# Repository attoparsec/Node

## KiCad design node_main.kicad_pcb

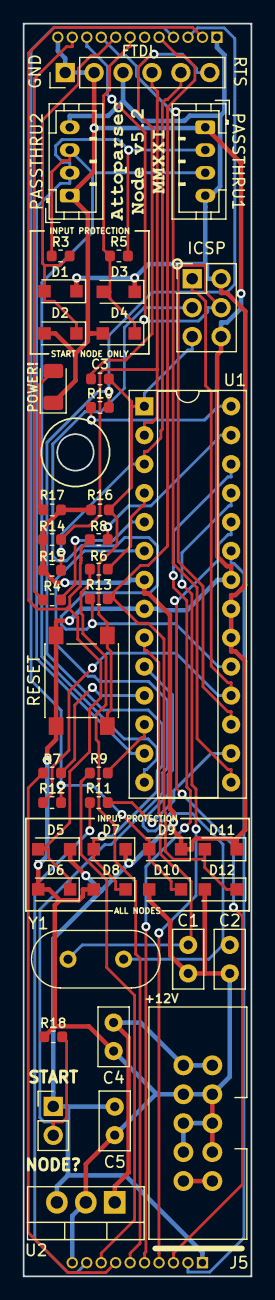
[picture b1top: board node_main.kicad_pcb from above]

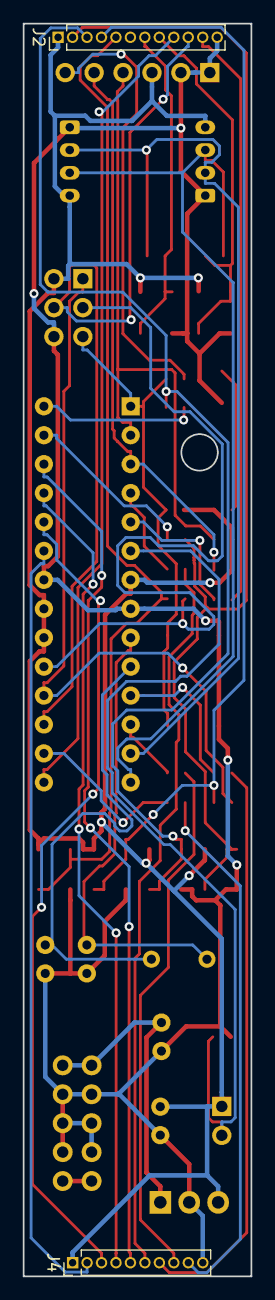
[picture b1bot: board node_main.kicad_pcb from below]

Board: 2 copper layers, 20.0 x 110.0 mm, 46 parts (2 on the bottom side), 40 nets.

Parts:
C1, C2: 22p; C_Disc_D5.0mm_W2.5mm_P2.50mm
C3: 100nF; C_0603_1608Metric
C4: 0.33U; C_Disc_D5.0mm_W2.5mm_P2.50mm
C5: 0.01U; C_Disc_D5.0mm_W2.5mm_P2.50mm
D1, D2, D3, D4, D5, D6, D7, D8, D9, D10, D11, D12: Bat85; D_SOD-123F
FTDI: FTDI; PinHeader_1x06_P2.54mm_Vertical
ICSP: Conn_02x03_Male; PinHeader_2x03_P2.54mm_Vertical
J2: Conn_01x12_Male; PinHeader_1x12_P1.27mm_Vertical
J4: Conn_01x10_Male; PinHeader_1x10_P1.27mm_Vertical
J5: Conn_02x05_Odd_Even; Shrouded_power_header
PASSTHRU1, PASSTHRU2: Conn_01x04_Male; JST_PH_B4B-PH-K_1x04_P2.00mm_Vertical
POWER!: LED; LED_1206_3216Metric
R3, R4, R5, R6, R7, R8, R9, R10, R11, R12, R13, R14, R15, R16, R17, R18: 1K; R_0603_1608Metric
RESET: SW_SPST; SW_SPST_PTS645
START1: Conn_01x02_Male; PinHeader_1x02_P2.54mm_Vertical
U1: ATmega328P-PU; DIP-28_W7.62mm_Socket
U2: L7805; TO-220-3_Vertical
Y1: Crystal; Crystal_HC49-U_Vertical

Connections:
+5V: C5.1, D1.1, D3.1, D5.1, D7.1, D9.1, D11.1, FTDI.3, ICSP.2, J2.1, J4.1, PASSTHRU1.4, PASSTHRU2.4, R14.1, R15.1, R16.1, R17.2, START1.1, U1.7, U1.20, U1.21, U2.3
+12V: C4.1, J5.1, J5.2, U2.1
-12V: J5.9, J5.10
APIN_0: J4.2, U1.23
APIN_1: J4.3, U1.24
APIN_2: J4.4, U1.25
APIN_3: J4.5, U1.26
APIN_4: R8.1, U1.27
APIN_5: R10.1, U1.28
CLOCK_MAIN: PASSTHRU1.3, PASSTHRU2.3, R3.1, U1.14
CRYSTAL1: C1.2, U1.9, Y1.1
CRYSTAL2: C2.2, U1.10, Y1.2
DPIN_2: R6.2, U1.4
DPIN_4: R18.2, START1.2, U1.6
DPIN_7: PASSTHRU1.2, PASSTHRU2.2, R5.1, U1.13
GND: C1.1, C2.1, C4.2, C5.2, D2.2, D4.2, D6.2, D8.2, D10.2, D12.2, FTDI.1, FTDI.2, ICSP.6, J2.12, J4.10, J5.3, J5.4, J5.5, J5.6, J5.7, J5.8, PASSTHRU1.1, PASSTHRU2.1, POWER!.1, R18.1, RESET.2, U1.8, U1.22, U2.2
INPUT_1_MAIN_RAW: D5.2, D6.1, J2.2, R8.2
INPUT_2_MAIN_RAW: D7.2, D8.1, J2.3, R10.2
INPUT_3_MAIN: ICSP.1, R12.1, U1.18
INPUT_3_MAIN_RAW: D9.2, D10.1, J2.4, R12.2
INPUT_4_MAIN: ICSP.3, R13.1, U1.19
INPUT_4_MAIN_RAW: D11.2, D12.1, J2.5, R13.2
INPUT_CLOCK_MAIN_RAW: D1.2, D2.1, J2.8, R3.2
INPUT_RESET_MAIN_RAW: D3.2, D4.1, J2.7, R5.2
LED_MAIN: J2.9, U1.15
MOSI_PWM_DPIN_11: ICSP.4, J2.10, U1.17
unnamed: C3.2, FTDI.6
unnamed: POWER!.2, R17.1
OUTPUT_1_MAIN_RAW: J4.6, R6.1
OUTPUT_2_MAIN: R7.2, U1.11
OUTPUT_2_MAIN_RAW: J4.7, R7.1
OUTPUT_3_MAIN: R9.2, U1.12
OUTPUT_3_MAIN_RAW: J4.8, R9.1
OUTPUT_4_MAIN: R11.2, U1.16
OUTPUT_4_MAIN_RAW: J4.9, R11.1
OUTPUT_IDENT_MAIN: R4.2, U1.5
OUTPUT_IDENT_MAIN_RAW: J2.11, R4.1
RESET: C3.1, ICSP.5, R16.2, RESET.1, U1.1
RX_DPIN_0: FTDI.4, R14.2, U1.2
TX_DPIN_1: FTDI.5, R15.2, U1.3

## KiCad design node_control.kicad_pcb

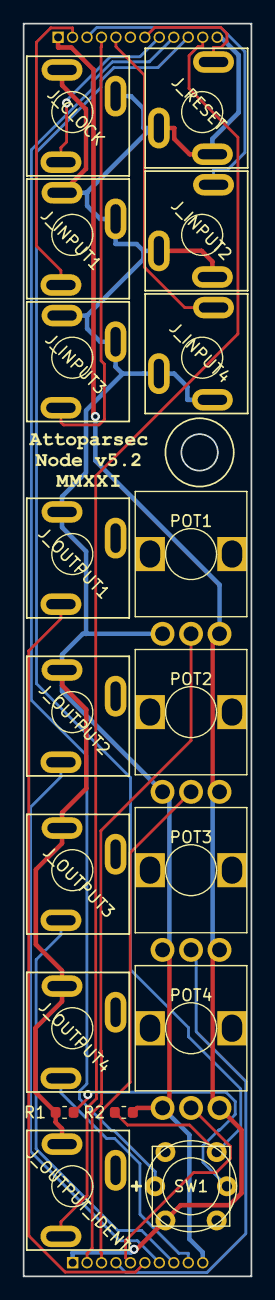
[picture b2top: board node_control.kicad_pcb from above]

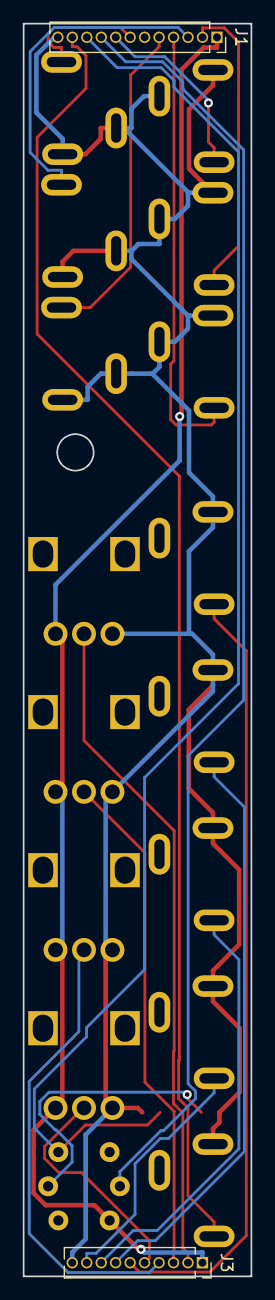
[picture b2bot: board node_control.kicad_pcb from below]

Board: 2 copper layers, 20.0 x 110.0 mm, 20 parts (2 on the bottom side), 20 nets.

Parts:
J1: Conn_01x12_Female; PinSocket_1x12_P1.27mm_Vertical
J3: Conn_01x10_Female; PinSocket_1x10_P1.27mm_Vertical
J_CLOCK: PJ301CM; PJ301
J_INPUT1, J_INPUT2, J_INPUT3, J_INPUT4: PJ301CM; PJ301
J_OUTPUT1, J_OUTPUT2, J_OUTPUT3, J_OUTPUT4: PJ301CM; PJ301
J_OUTPUT_IDENT: PJ301CM; PJ301
J_RESET: PJ301CM; PJ301
POT1, POT2, POT3, POT4: 10K; P090S_pot
R1, R2: 1K; R_0603_1608Metric
SW1: TL1265; TL1265_ILLUMINATED_TACTILE_SWITCH

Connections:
+5V: J1.1, J3.1, POT1.3, POT2.3, POT3.3, POT4.3, SW1.4
GND: J1.12, J3.10, J_CLOCK.1, J_CLOCK.2, J_INPUT1.1, J_INPUT1.2, J_INPUT2.1, J_INPUT2.2, J_INPUT3.1, J_INPUT3.2, J_INPUT4.1, J_INPUT4.2, J_OUTPUT1.1, J_OUTPUT2.1, J_OUTPUT3.1, J_OUTPUT4.1, J_OUTPUT_IDENT.1, J_RESET.1, J_RESET.2, POT1.1, POT2.1, POT3.1, POT4.1, R1.1, R2.1
INPUT_1_CONT: J1.2, J_INPUT1.3
INPUT_2_CONT: J1.3, J_INPUT2.3
INPUT_3_CONT: J1.4, J_INPUT3.3
INPUT_4_CONT: J1.5, J_INPUT4.3
INPUT_CLOCK_CONT: J1.8, J_CLOCK.3
INPUT_RESET_CONT: J1.7, J_RESET.3
LED_CONT: J1.9, SW1.6
unnamed: R1.2, SW1.5
OUTPUT_1_CONT: J3.6, J_OUTPUT1.3
OUTPUT_2_CONT: J3.7, J_OUTPUT2.3
OUTPUT_3_CONT: J3.8, J_OUTPUT3.3
OUTPUT_4_CONT: J3.9, J_OUTPUT4.3
OUTPUT_IDENT_CONT: J1.11, J_OUTPUT_IDENT.3
POT_1_CONT: J3.2, POT1.2
POT_2_CONT: J3.3, POT2.2
POT_3_CONT: J3.4, POT3.2
POT_4_CONT: J3.5, POT4.2
SWITCH_CONT: J1.10, R2.2, SW1.1
